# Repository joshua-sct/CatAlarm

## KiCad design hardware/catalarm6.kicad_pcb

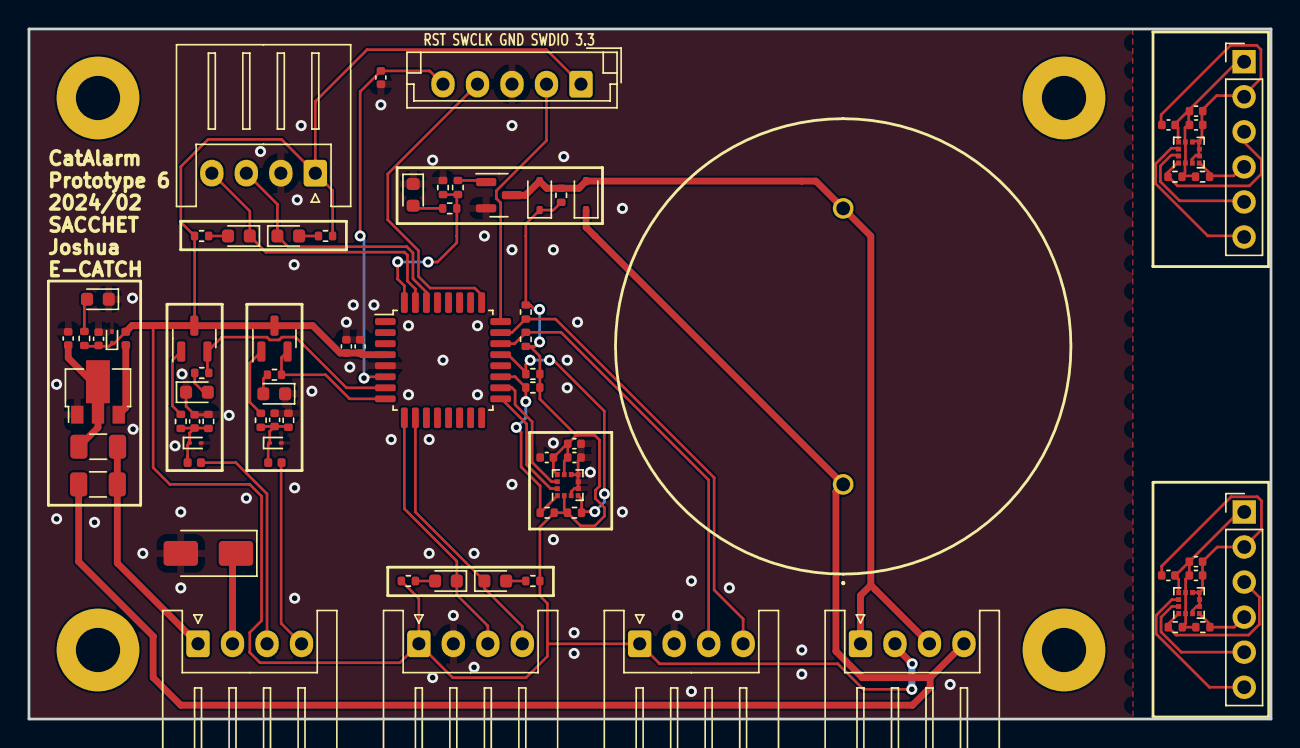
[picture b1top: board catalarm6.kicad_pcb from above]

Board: 2 copper layers, 90.0 x 50.0 mm, 81 parts (0 on the bottom side), 51 nets.

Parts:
C1, C2, C6, C8, C10, C11, C12, C14, C15: 100nF; C_0402_1005Metric
C3: 4.7uF; C_0402_1005Metric
C4, C9, C13, C16: 10uF; C_0402_1005Metric
C5, C7: 1nF; C_0402_1005Metric
CON1, CON3, CON4, CON5, CON6: JST_04; JST_XH_S4B-XH-A_1x04_P2.50mm_Horizontal
CON2: JST_05; JST_EH_B5B-EH-A_1x05_P2.50mm_Vertical
D1: SS14; D_SMA
D4, D5, D6: onsemi ESD9B3.3ST5G; D_SOD-923
D_out2, D_out3: D_Schottky; D_SOD-323
F1, F2: JK-nSMD030/16V; Fuse_1206_3216Metric
FB1, FB2, FB3: FerriteBead_Small; L_0402_1005Metric
H1, H2, H3, H4: M3_Hole_With_Spacer_H10mm; MountingHole_3.2mm_With_Spacer_H10mm
J1, J2: PINHD_1x6_Male; PinHeader_1x06_P2.54mm_Vertical
LED1, LED2, LED3, LED4, LED5, LED6, LED7, LED8: LED; LED_0603_1608Metric
LS1: PS-953Q; PS953Q
Q1, Q4, Q6: IRLML6244; SOT-23
R1, R2, R3, R5, R8, R16, R23, R25: 10k; R_0402_1005Metric
R4, R7, R10, R11, R12, R13, R14, R15, R17, R18, R19, R20, R21, R22: 4.7k; R_0402_1005Metric
R6, R9, R24: 10; R_0402_1005Metric
U1: HT7533-3 -1-SOT89; SOT-89-3
U2: STM32G030K8Tx; LQFP-32_7x7mm_P0.8mm
U3, U4, U5: LIS2DW12TR; LGA-12_2x2mm_P0.5mm

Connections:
+3.3V: C3.2, C4.2, C6.2, C8.2, C9.2, C10.2, CON2.1, CON3.2, CON4.1, CON5.1, CON6.1, D6.1 (K), D_out2.1 (K), FB1.2, Q1.3 (D), Q4.3 (D), R1.2, R4.1, R7.2, R10.1, R11.2, R12.1, R13.2, R14.1, R15.1, R17.1, R18.1, R25.1, U2.4 (VDD), U3.2 (~CS), U3.9 (Vdd), U3.10 (Vdd_IO)
/3.3ext: C11.2, C12.2, C13.2, J1.1, R19.1, R20.2, U4.2 (~CS), U4.9 (Vdd), U4.10 (Vdd_IO)
/3.3ext2: C14.2, C15.2, C16.2, J2.1, R21.1, R22.2, U5.2 (~CS), U5.9 (Vdd), U5.10 (Vdd_IO)
/+12V: CON3.4, D_out3.1 (K), F2.2, LS1.1 (+)
/BAT: CON1.1, F1.1, F2.1
/BLK: Q1.2 (S), R2.2, U2.8 (PA1)
/BLK_in: CON1.4, FB3.1
/GNDext: C11.1, C12.1, C13.1, J1.2, U4.3 (SA0/SDO), U4.5 (RES), U4.6 (GND), U4.7 (GND), U4.8 (GND)
/GNDext2: C14.1, C15.1, C16.1, J2.2, U5.3 (SA0/SDO), U5.5 (RES), U5.6 (GND), U5.7 (GND), U5.8 (GND)
/INT1: U2.17 (PB2), U3.12 (INT1)
/INT1ext: J1.5, U4.12 (INT1)
/INT1ext2: J2.5, U5.12 (INT1)
/INT2: U2.18 (PA8), U3.11 (INT2)
/INT2ext: J1.6, U4.11 (INT2)
/INT2ext2: J2.6, U5.11 (INT2)
/RESET: C2.2, CON2.5, U2.6 (NRST)
/SCL: R4.2, R12.2, U2.19 (PA9/NC), U3.1 (SCL/SPC)
/SCL2: CON4.3, R10.2, U2.22 (PA11/PA9)
/SCLext: J1.3, R19.2, U4.1 (SCL/SPC)
/SCLext2: J2.3, R21.2, U5.1 (SCL/SPC)
/SDA: R7.1, R13.1, U2.21 (PA10/NC), U3.4 (SDA/SDI)
/SDA2: CON4.4, R11.1, U2.23 (PA12/PA10)
/SDAext: J1.4, R20.1, U4.4 (SDA/SDI)
/SDAext2: J2.4, R22.1, U5.4 (SDA/SDI)
/SWCLK: CON2.4, U2.25 (PA14)
/SWDIO: CON2.2, U2.24 (PA13)
/USART1_RX: CON6.4, LED8.1 (K), U2.31 (PB7)
/USART1_TX: CON6.3, LED6.1 (K), U2.30 (PB6)
/USART2_RX: CON5.4, LED7.1 (K), U2.10 (PA3)
/USART2_TX: CON5.3, LED5.1 (K), U2.9 (PA2)
/acc: Q4.2 (S), R3.2, U2.7 (PA0)
/acc_in: CON1.3, FB2.1
/out: R16.1, R23.1, R24.1, U2.32 (PB8)
GND: C1.1, C2.1, C3.1, C4.1, C5.1, C6.1, C7.1, C8.1, C9.1, C10.1, CON2.3, CON4.2, CON5.2, CON6.2, D1.2 (A), D4.2 (A), D5.2 (A), D6.2 (A), LED1.1 (K), LED2.1 (K), LED3.1 (K), LED4.1 (K), Q6.2 (S), R5.2, R8.2, R16.2, U1.1 (GND), U2.5 (VSS), U3.3 (SA0/SDO), U3.5 (RES), U3.6 (GND), U3.7 (GND), U3.8 (GND)
unnamed: CON1.2, D1.1 (K)
unnamed: C5.2, D4.1 (K), FB2.2, R8.1, R9.1
unnamed: C7.2, D5.1 (K), FB3.2, R5.1, R6.1
unnamed: CON3.1, CON3.3, D_out2.2 (A), D_out3.2 (A), LS1.2 (-), Q6.3 (D), R25.2
unnamed: LED1.2 (A), R3.1
unnamed: LED2.2 (A), R2.1
unnamed: LED3.2 (A), R23.2
unnamed: LED4.2 (A), R1.1
unnamed: LED5.2 (A), R17.2
unnamed: LED6.2 (A), R14.2
unnamed: LED7.2 (A), R18.2
unnamed: LED8.2 (A), R15.2
unnamed: Q1.1 (G), R6.2
unnamed: Q4.1 (G), R9.2
unnamed: Q6.1 (G), R24.2
unnamed: C1.2, F1.2, U1.2 (VIN)
unnamed: FB1.1, U1.3 (VOUT)

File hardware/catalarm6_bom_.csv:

Component,Description,Part,References,Value,Footprint,Quantity Per PCB,Datasheet,LCSC Part Number,Manufacturer_Part_Number,NAMEALIAS,SPICEPRE,SPICESYMBOLNAME,Digikey Part Number,Height,Manufacturer_Name,Mouser Part Number,Mouser Price/Stock,RESISTANCE (OHMS)
1,Unpolarized Capacitor,Capacitor_NP,C5 C7,1nF,C_0402_1005Metric,2,,C696907,TCC0402X7R102M500AT,,,,,,,,,
2,,root_1_100nF,C1 C6 C8 C10 C11 C12 C14 C15,100nF,C_0402_1005Metric,8,,C392963,TCC0402X7R104K160AT,Value,C,0603B104K500NT,,,,,,
3,,root_2_100nf,C2,100nF,C_0402_1005Metric,1,,C392963,TCC0402X7R104K160AT,Value(F),C,C_0603_US,,,,,,
4,,root_1_4.7uF,C3,4.7uF,C_0402_1005Metric,1,,C307423,CL05A475MQ5NRNC,Value(F),C,C_0603_US,,,,,,
5,,root_1_4.7uF,C4 C9 C13 C16,10uF,C_0402_1005Metric,4,,C15525,CL05A106MQ5NUNC,Value(F),C,C_0603_US,,,,,,
6,JST Connector  4 pins ,JST_04,CON1 CON3 CON4 CON5 CON6,JST_04,JST_XH_S4B-XH-A_1x04_P2.50mm_Horizontal,5,,C157925,S4B-XH-A(LF)(SN),,,,455-2243-ND,,,,,
7,Schottky diode,D_Schottky,D_out2 D_out3,D_Schottky,D_SOD-323,2,~,C150185,"1SS367,H3F",,,,,,,,,
8,Shockley (PNPN) diode,D_Shockley,D1,SS14,D_SMA,1,~,C2480,SS14,,,,,,,,,
9,"ESD Protection Diode, SOD-523",ESD5Zxx,D4 D5 D6,onsemi ESD9B3.3ST5G ,D_SOD-923,3,https://www.onsemi.com/pdf/datasheet/esd5z2.5t1-d.pdf,C96512,onsemi ESD9B3.3ST5G,,,,,,,,,
10,Fuse,Fuse,F1 F2, JK-nSMD030/16V,Fuse_1206_3216Metric,2,~,C2830239,JK-nSMD030/16V,,,,,,,,,
11,"Ferrite bead, small symbol",FerriteBead_Small,FB1 FB2 FB3,FerriteBead_Small,L_0402_1005Metric,3,~,C316267,CB1005-600(f),,,,,,,,,
12,Light emitting diode,LED,LED1 LED2 LED3 LED4 LED5 LED6 LED7 LED8,LED,LED_0603_1608Metric,8,~,C965799,XL-1608SURC-06,,,,,,,,,
13,"Piezo Buzzers & Audio Indicators SIREN, 5-15VDC 105DB, PC PINS",PS-953Q,LS1,PS-953Q,PS953Q,1,https://componentsearchengine.com/Datasheets/1/PS-953Q.pdf,C6737823,PS-953Q,,,,,33.2,Mallory Sonalert,539-PS-953Q,https://www.mouser.com/Search/Refine.aspx?Keyword=539-PS-953Q,
14,"6.3A Id, 20V Vds, 21mOhm Rds, N-Channel StrongIRFET Power MOSFET, SOT-23",IRLML6244,Q1 Q4 Q6,IRLML6244,SOT-23,3,https://www.infineon.com/dgdl/Infineon-IRLML6244-DataSheet-v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,C143946,IRLML6244,,,,,,,,,
15,Resistor,R,R6 R9 R24,10,R_0402_1005Metric,3,~,C102753,RTT02100JTH,,,,,,,,,
16,,root_3_4.7kΩ,R4 R10 R12 R19 R21,4.7k,R_0402_1005Metric,5,,C2906941,FRC0402J472 TS,Resistance,R,0603WAF4701T5E,,,,,,4.7K
17,,root_1_4.7kΩ,R7 R11 R13 R20 R22,4.7k,R_0402_1005Metric,5,,C2906941,FRC0402J472 TS,Resistance,R,0603WAF4701T5E,,,,,,4.7K
18,,root_1_1k,R14 R15 R17 R18,4.7k,R_0402_1005Metric,4,,C2906941,FRC0402J472 TS,Value(Ω),R,Resistor,,,,,,
19,,root_1_1k,R1 R2 R3,10k,R_0402_1005Metric,3,,C2906885,FRC0402J103 TS,Value(Ω),R,Resistor,,,,,,
20,Resistor,R,R5 R8 R16 R23 R25,10k,R_0402_1005Metric,5,~,C2906885,FRC0402J103 TS,,,,,,,,,
21,"100mA Low Dropout Voltage Regulator, Fixed Output, SOT89",HT75xx-1-SOT89,U1,HT7533-3 -1-SOT89 ,SOT-89-3,1,https://www.holtek.com/documents/10179/116711/HT75xx-1v250.pdf,C7470656,HT7533-3,,,,,,,,,
22,"3-Axis Accelerometer, 2/4/8/16g range, I2C/SPI interface",LIS2DE12,U3 U4 U5,LIS2DW12TR,LGA-12_2x2mm_P0.5mm,3,https://www.st.com/resource/en/datasheet/lis2DE12.pdf,C189624,LIS2DW12TR,,,,,,,,,
23,"STMicroelectronics Arm Cortex-M0+ MCU, 64KB flash, 8KB RAM, 64 MHz, 2.0-3.6V, 29 GPIO, LQFP32",STM32G030K8Tx,U2,STM32G030K8Tx,LQFP-32_7x7mm_P0.8mm,1,https://www.st.com/resource/en/datasheet/stm32g030k8.pdf,C431631,STM32G030K8T6,,,,497-19770-ND,,,,,





Component Groups:,23
Component Count:,74
Fitted Components:,74
Number of PCBs:,1
Total components:,74
Schematic Version:,
Schematic Date:,
PCB Variant:,default
BoM Date:,2/12/2024 10:06:49 PM
Schematic Source:,catalarm6.kicad_sch
KiCad Version:,Eeschema 7.0.8

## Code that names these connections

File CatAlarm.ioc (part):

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Mcu.Name=STM32G030K(6-8)Tx
Mcu.Package=LQFP32
Mcu.UserName=STM32G030K8Tx
PA0.GPIOParameters=GPIO_Label
PA0.GPIO_Label=ACC
PA0.Signal=GPXTI0
PA1.GPIOParameters=GPIO_Label,GPIO_ModeDefaultEXTI
PA1.GPIO_Label=BLK
PA1.GPIO_ModeDefaultEXTI=GPIO_MODE_IT_RISING
PA1.Signal=GPXTI1
PA10.GPIOParameters=GPIO_Label
PA10.GPIO_Label=AIN_SDA
PA10.Mode=I2C
PA10.Signal=I2C1_SDA
PA11\ [PA9].GPIOParameters=GPIO_Label
PA11\ [PA9].GPIO_Label=AOUT_SCL
PA11\ [PA9].Mode=I2C
PA11\ [PA9].Signal=I2C2_SCL
PA12\ [PA10].GPIOParameters=GPIO_Label
PA12\ [PA10].GPIO_Label=AOUT_SDA
PA12\ [PA10].Mode=I2C
PA12\ [PA10].Signal=I2C2_SDA
PA13.Mode=Serial_Wire
PA13.Signal=SYS_SWDIO
PA14-BOOT0.Mode=Serial_Wire
PA14-BOOT0.Signal=SYS_SWCLK
PA2.Mode=Asynchronous
PA2.Signal=USART2_TX
PA3.Mode=Asynchronous
PA3.Signal=USART2_RX
PA8.GPIOParameters=GPIO_Label
PA8.GPIO_Label=AIN_INT2
PA8.Signal=GPXTI8
PA9.GPIOParameters=GPIO_Label
PA9.GPIO_Label=AIN_SCL
PA9.Mode=I2C
PA9.Signal=I2C1_SCL
PB2.GPIOParameters=GPIO_Label
PB2.GPIO_Label=AIN_INT1
PB2.Signal=GPXTI2
PB6.Mode=Asynchronous
PB6.Signal=USART1_TX
PB7.Mode=Asynchronous
PB7.Signal=USART1_RX
PB8.GPIOParameters=GPIO_Label
PB8.GPIO_Label=BUZZER
PB8.Signal=GPIO_Output
RCC.HSE_VALUE=8000000
RCC.SYSCLKFreq_VALUE=16000000
board=custom

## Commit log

2023-03-29 git checkout test
2024-01-09 v4_0109
2024-01-10 0110
2024-01-11 240111
2024-03-09 Accel lib cpp
2024-03-11 Commencé à fusionner avec les modules cpp du programme arduino
2024-03-11 Commencé à intégré les Log et les "trop sonné" pour la Siren
2024-03-11 Essais RTC
2024-03-12 Ecriture des méthodes pour la structure Log
2024-03-12 Erreurs de compilations
2024-03-12 Essais Timestamp UNIX
2024-03-13 Utilisation de timestamp unix partout + Singleton (checkpoint)
2024-03-13 Injection de dépendances pour Log dans Siren
2024-03-13 Erreurs de compilation éliminées
2024-03-14 Modifs main/Siren/global
2024-03-14 Modifs Accel/global
2024-03-14 Accel et Log fonctionnent bien
2024-03-23 Maquette : Contournement problème CEM
2024-03-23 [à tester] Contournement 3 PB CEM Voiture
2025-02-18 Create LICENSE
2025-02-18 Create hardware branch
2025-02-18 Create software folder
2025-02-18 Project reorganisation
2025-02-18 Added a french trifold about the product
